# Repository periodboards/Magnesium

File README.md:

# Magnesium
My crappy 14-key macropad that contains many mistakes in the design

## Errors
### RGB backlighting doesn't work
Somehow in the many days that I had worked on routing the backlighting, I never noticed that I used the wrong LED footprint and so the leds are on the wrong side of the board

### The WS2812 was wired incorrectly
The power and ground were swapped on the WS2812, and therefore if you want to have underglow you need to use a bodge wire to connect data in to what was data out and rotate all of the LEDs accordingly

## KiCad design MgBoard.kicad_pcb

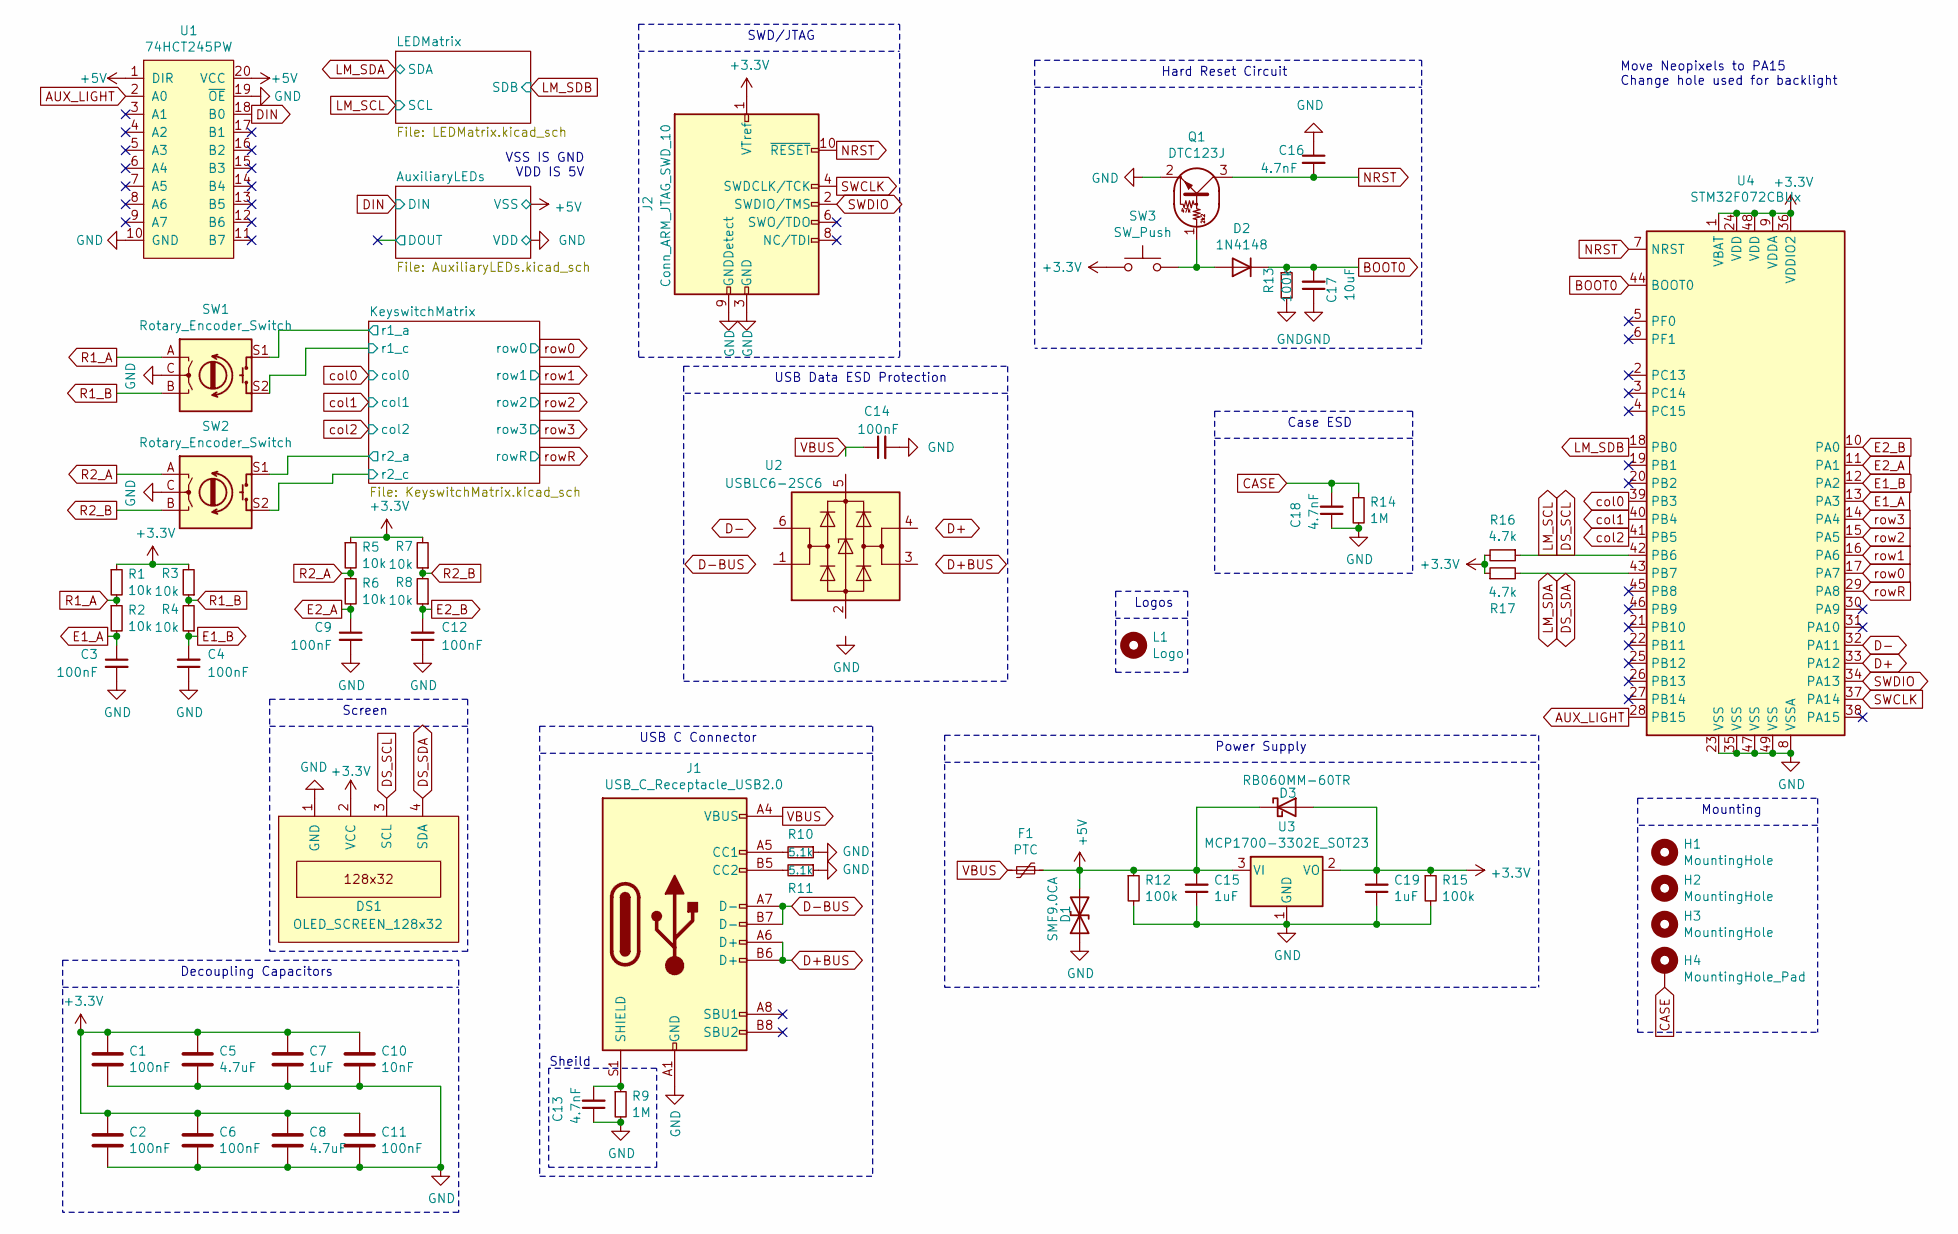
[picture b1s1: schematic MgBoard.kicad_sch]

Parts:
C1, C2, C3, C4, C6, C9, C11, C12, C14: 100nF; C_0603_1608Metric_Pad1.05x0.95mm_HandSolder
C5, C8: 4.7uF; C_0603_1608Metric_Pad1.05x0.95mm_HandSolder
C7, C15, C19: 1uF; C_0603_1608Metric_Pad1.05x0.95mm_HandSolder
C10: 10nF; C_0603_1608Metric_Pad1.05x0.95mm_HandSolder
C13, C16, C18: 4.7nF; C_0603_1608Metric_Pad1.05x0.95mm_HandSolder
C17: 10uF; C_0603_1608Metric_Pad1.05x0.95mm_HandSolder
D1: SMF9.0CA; D_SOD-123F
D2: 1N4148; D_SOD-123
D3: RB060MM-60TR; D_SOD-123F
DS1: OLED_SCREEN_128x32
F1: PTC; Fuse_1206_3216Metric_Pad1.42x1.75mm_HandSolder
H1, H2, H3: MountingHole; MountingHole_3.2mm_M3_ISO14580
H4: MountingHole_Pad; MountingHole_3.2mm_M3_ISO14580_Pad
J1: USB_C_Receptacle_USB2.0; USB_C_Receptacle_HRO_TYPE-C-31-M-12
J2: Conn_ARM_JTAG_SWD_10; PinHeader_2x05_P2.54mm_Vertical
L1: Logo; Mg
Q1: DTC123J; SOT-323_SC-70_Handsoldering
R1, R2, R3, R4, R5, R6, R7, R8: 10k; R_0603_1608Metric_Pad1.05x0.95mm_HandSolder
R9, R14: 1M; R_0603_1608Metric_Pad1.05x0.95mm_HandSolder
R10, R11: 5.1k; R_0603_1608Metric_Pad1.05x0.95mm_HandSolder
R12, R13, R15: 100k; R_0603_1608Metric_Pad1.05x0.95mm_HandSolder
R16, R17: 4.7k; R_0603_1608Metric_Pad1.05x0.95mm_HandSolder
SW1, SW2: Rotary_Encoder_Switch; RotaryEncoder_Alps_EC11E-Switch_Vertical_H20mm_1u
SW3: SW_Push; SW_SPST_SKQG_WithStem
U1: 74HCT245PW; TSSOP-20_4.4x6.5mm_P0.65mm
U2: USBLC6-2SC6; SOT-23-6_Handsoldering
U3: MCP1700-3302E_SOT23; SOT-23_Handsoldering
U4: STM32F072CBUx; QFN-48-1EP_7x7mm_P0.5mm_EP5.6x5.6mm

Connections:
+3V3: C1.1, C2.1, C5.1, C6.1, C7.1, C8.1, C10.1, C11.1, C19.2, D3.2 (A), DS1.2 (VCC), J2.1 (VTref), R1.1, R3.2, R5.1, R7.2, R15.1, R16.2, R17.1, SW3.1, U3.2 (VO), U4.1 (VBAT), U4.9 (VDDA), U4.24 (VDD), U4.36 (VDDIO2), U4.48 (VDD); also elsewhere on the board
+5V: C15.2, D1.2 (A2), D3.1 (K), F1.1, R12.1, U1.1 (DIR), U1.20 (VCC), U3.3 (VI); also elsewhere on the board
/KeyswitchMatrix/r1_c: SW1.S2; also elsewhere on the board
/KeyswitchMatrix/r2_c: SW2.S2; also elsewhere on the board
AUX_LIGHT: U1.2 (A0), U4.28 (PB15)
BOOT0: C17.2, D2.1 (K), R13.1, U4.44 (BOOT0)
CASE: C18.2, H4.1, R14.1
D+: U2.4 (I/O2), U4.33 (PA12)
D+BUS: J1.A6 (D+), J1.B6 (D+), U2.3 (I/O2)
D-: U2.6 (I/O1), U4.32 (PA11)
D-BUS: J1.A7 (D-), J1.B7 (D-), U2.1 (I/O1)
DIN: U1.18 (B0); also elsewhere on the board
DS_SCL: DS1.3 (SCL), R16.1, U4.42 (PB6); also elsewhere on the board
DS_SDA: DS1.4 (SDA), R17.2, U4.43 (PB7); also elsewhere on the board
E1_A: C3.1, R2.2, U4.13 (PA3)
E1_B: C4.2, R4.1, U4.12 (PA2)
E2_A: C9.1, R6.2, U4.11 (PA1)
E2_B: C12.2, R8.1, U4.10 (PA0)
GND: C1.2, C2.2, C3.2, C4.1, C5.2, C6.2, C7.2, C8.2, C9.2, C10.2, C11.2, C12.1, C13.1, C14.2, C15.1, C16.1, C17.1, C18.1, C19.1, D1.1 (A1), DS1.1 (GND), J1.A1 (GND), J1.A12 (GND), J1.B1 (GND), J1.B12 (GND), J2.3 (GND), J2.5 (GND), J2.9 (GNDDetect), Q1.2 (E), R9.2, R10.1, R11.1, R12.2, R13.2, R14.2, R15.2, SW1.C, SW2.C, U1.10 (GND), U1.19 (~OE), U2.2 (GND), U3.1 (GND), U4.8 (VSSA), U4.23 (VSS), U4.35 (VSS), U4.47 (VSS), U4.49 (VSS); also elsewhere on the board
LM_SDB: U4.18 (PB0); also elsewhere on the board
NRST: C16.2, J2.10 (~RESET~), Q1.3 (C), U4.7 (NRST)
unnamed: C13.2, J1.S1 (SHIELD), R9.1
unnamed: D2.2 (A), Q1.1 (B), SW3.2
unnamed: J1.A5 (CC1), R10.2
unnamed: J1.B5 (CC2), R11.2
R1_A: R1.2, R2.1, SW1.A
R1_B: R3.1, R4.2, SW1.B
R2_A: R5.2, R6.1, SW2.A
R2_B: R7.1, R8.2, SW2.B
SWCLK: J2.4 (SWDCLK/TCK), U4.37 (PA14)
SWDIO: J2.2 (SWDIO/TMS), U4.34 (PA13)
VBUS: C14.1, F1.2, J1.A4 (VBUS), J1.A9 (VBUS), J1.B4 (VBUS), J1.B9 (VBUS), U2.5 (VBUS)
col0: SW1.S1, U4.39 (PB3); also elsewhere on the board
col1: U4.40 (PB4); also elsewhere on the board
col2: SW2.S1, U4.41 (PB5); also elsewhere on the board
row0: U4.17 (PA7); also elsewhere on the board
row1: U4.16 (PA6); also elsewhere on the board
row2: U4.15 (PA5); also elsewhere on the board
row3: U4.14 (PA4); also elsewhere on the board
rowR: U4.29 (PA8); also elsewhere on the board

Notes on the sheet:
Decoupling Capacitors
Screen
Sheild
VSS IS GND VDD IS 5V
USB C Connector
SWD/JTAG
USB Data ESD Protection
Logos
Hard Reset Circuit
Power Supply
Case ESD
Move Neopixels to PA15 Change hole used for backlight
Mounting

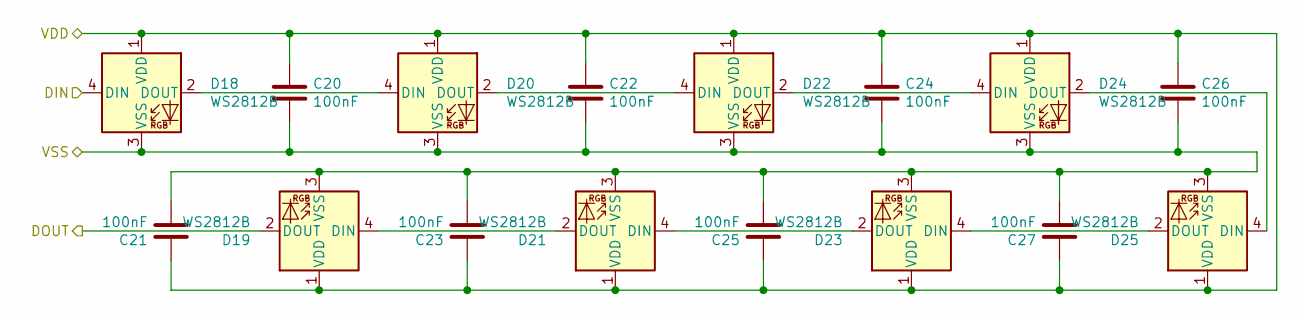
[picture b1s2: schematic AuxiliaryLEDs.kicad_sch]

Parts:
C20, C21, C22, C23, C24, C25, C26, C27: 100nF; C_0603_1608Metric_Pad1.05x0.95mm_HandSolder
D18, D19, D20, D21, D22, D23, D24, D25: WS2812B; LED_WS2812B_PLCC4_5.0x5.0mm_P3.2mm

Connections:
+5V: C20.1, C21.1, C22.1, C23.1, C24.1, C25.1, C26.1, C27.1, D18.3 (VSS), D19.3 (VSS), D20.3 (VSS), D21.3 (VSS), D22.3 (VSS), D23.3 (VSS), D24.3 (VSS), D25.3 (VSS); also elsewhere on the board
/AuxiliaryLEDs/DOUT: D19.2 (DOUT)
DIN: D18.4 (DIN); also elsewhere on the board
GND: C20.2, C21.2, C22.2, C23.2, C24.2, C25.2, C26.2, C27.2, D18.1 (VDD), D19.1 (VDD), D20.1 (VDD), D21.1 (VDD), D22.1 (VDD), D23.1 (VDD), D24.1 (VDD), D25.1 (VDD); also elsewhere on the board
unnamed: D18.2 (DOUT), D20.4 (DIN)
unnamed: D19.4 (DIN), D21.2 (DOUT)
unnamed: D20.2 (DOUT), D22.4 (DIN)
unnamed: D21.4 (DIN), D23.2 (DOUT)
unnamed: D22.2 (DOUT), D24.4 (DIN)
unnamed: D23.4 (DIN), D25.2 (DOUT)
unnamed: D24.2 (DOUT), D25.4 (DIN)

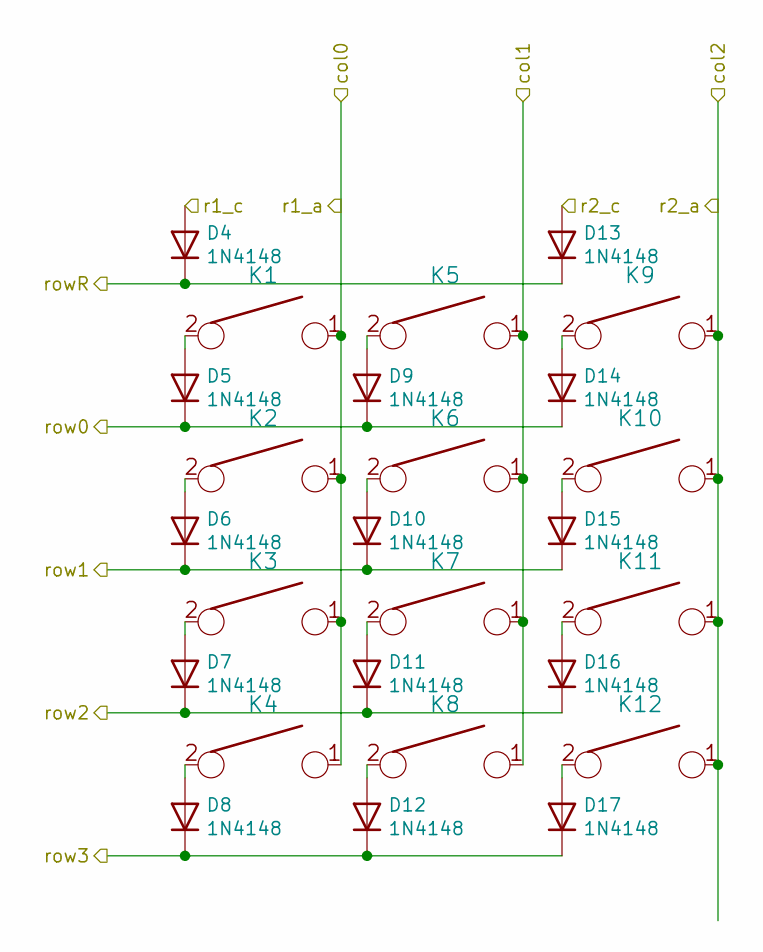
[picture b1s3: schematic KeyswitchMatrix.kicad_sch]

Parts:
D4, D5, D6, D7, D8, D9, D10, D11, D12, D13, D14, D15, D16, D17: 1N4148; D_SOD-123
K1, K2, K3, K4, K5, K6, K7, K8, K9, K10, K11, K12: KEYSW; Kailh_socket_MX_optional_1u

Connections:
/KeyswitchMatrix/r1_c: D4.2 (A); also elsewhere on the board
/KeyswitchMatrix/r2_c: D13.2 (A); also elsewhere on the board
unnamed: D5.2 (A), K1.2
unnamed: D6.2 (A), K2.2
unnamed: D7.2 (A), K3.2
unnamed: D8.2 (A), K4.2
unnamed: D9.2 (A), K5.2
unnamed: D10.2 (A), K6.2
unnamed: D11.2 (A), K7.2
unnamed: D12.2 (A), K8.2
unnamed: D14.2 (A), K9.2
unnamed: D15.2 (A), K10.2
unnamed: D16.2 (A), K11.2
unnamed: D17.2 (A), K12.2
col0: K1.1, K2.1, K3.1, K4.1; also elsewhere on the board
col1: K5.1, K6.1, K7.1, K8.1; also elsewhere on the board
col2: K9.1, K10.1, K11.1, K12.1; also elsewhere on the board
row0: D5.1 (K), D9.1 (K), D14.1 (K); also elsewhere on the board
row1: D6.1 (K), D10.1 (K), D15.1 (K); also elsewhere on the board
row2: D7.1 (K), D11.1 (K), D16.1 (K); also elsewhere on the board
row3: D8.1 (K), D12.1 (K), D17.1 (K); also elsewhere on the board
rowR: D4.1 (K), D13.1 (K); also elsewhere on the board

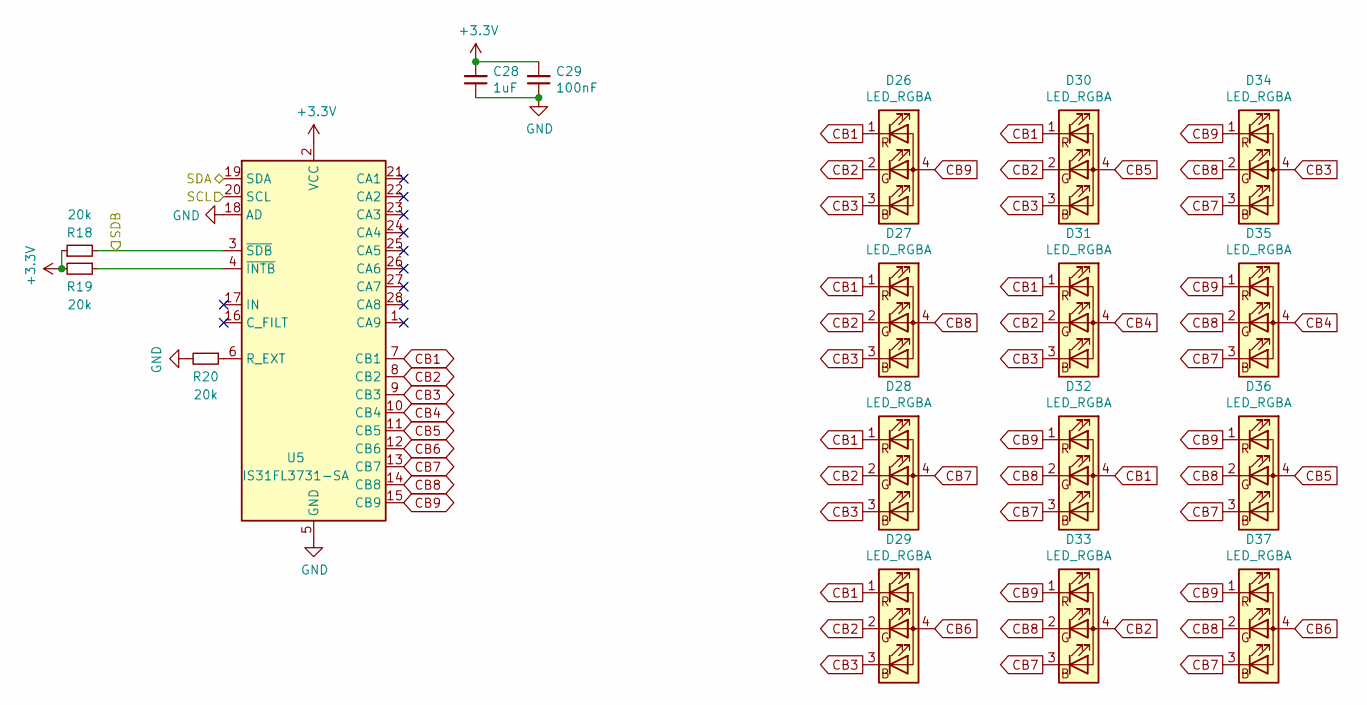
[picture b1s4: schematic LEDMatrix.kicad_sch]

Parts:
C28: 1uF; C_0603_1608Metric_Pad1.05x0.95mm_HandSolder
C29: 100nF; C_0603_1608Metric_Pad1.05x0.95mm_HandSolder
D26, D27, D28, D29, D30, D31, D32, D33, D34, D35, D36, D37: LED_RGBA; LED_RGBA_Reverse
R18, R19, R20: 20k; R_0603_1608Metric_Pad1.05x0.95mm_HandSolder
U5: IS31FL3731-SA; SSOP-28_5.3x10.2mm_P0.65mm

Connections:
+3V3: C28.2, C29.2, R18.1, R19.2, U5.2 (VCC); also elsewhere on the board
CB1: D26.1 (RK), D27.1 (RK), D28.1 (RK), D29.1 (RK), D30.1 (RK), D31.1 (RK), D32.4 (A), U5.7 (CB1)
CB2: D26.2 (GK), D27.2 (GK), D28.2 (GK), D29.2 (GK), D30.2 (GK), D31.2 (GK), D33.4 (A), U5.8 (CB2)
CB3: D26.3 (BK), D27.3 (BK), D28.3 (BK), D29.3 (BK), D30.3 (BK), D31.3 (BK), D34.4 (A), U5.9 (CB3)
CB4: D31.4 (A), D35.4 (A), U5.10 (CB4)
CB5: D30.4 (A), D36.4 (A), U5.11 (CB5)
CB6: D29.4 (A), D37.4 (A), U5.12 (CB6)
CB7: D28.4 (A), D32.3 (BK), D33.3 (BK), D34.3 (BK), D35.3 (BK), D36.3 (BK), D37.3 (BK), U5.13 (CB7)
CB8: D27.4 (A), D32.2 (GK), D33.2 (GK), D34.2 (GK), D35.2 (GK), D36.2 (GK), D37.2 (GK), U5.14 (CB8)
CB9: D26.4 (A), D32.1 (RK), D33.1 (RK), D34.1 (RK), D35.1 (RK), D36.1 (RK), D37.1 (RK), U5.15 (CB9)
DS_SCL: U5.20 (SCL); also elsewhere on the board
DS_SDA: U5.19 (SDA); also elsewhere on the board
GND: C28.1, C29.1, R20.2, U5.5 (GND), U5.18 (AD); also elsewhere on the board
LM_SDB: R18.2, U5.3 (~SDB); also elsewhere on the board
unnamed: R19.1, U5.4 (~INTB)
unnamed: R20.1, U5.6 (R_EXT)

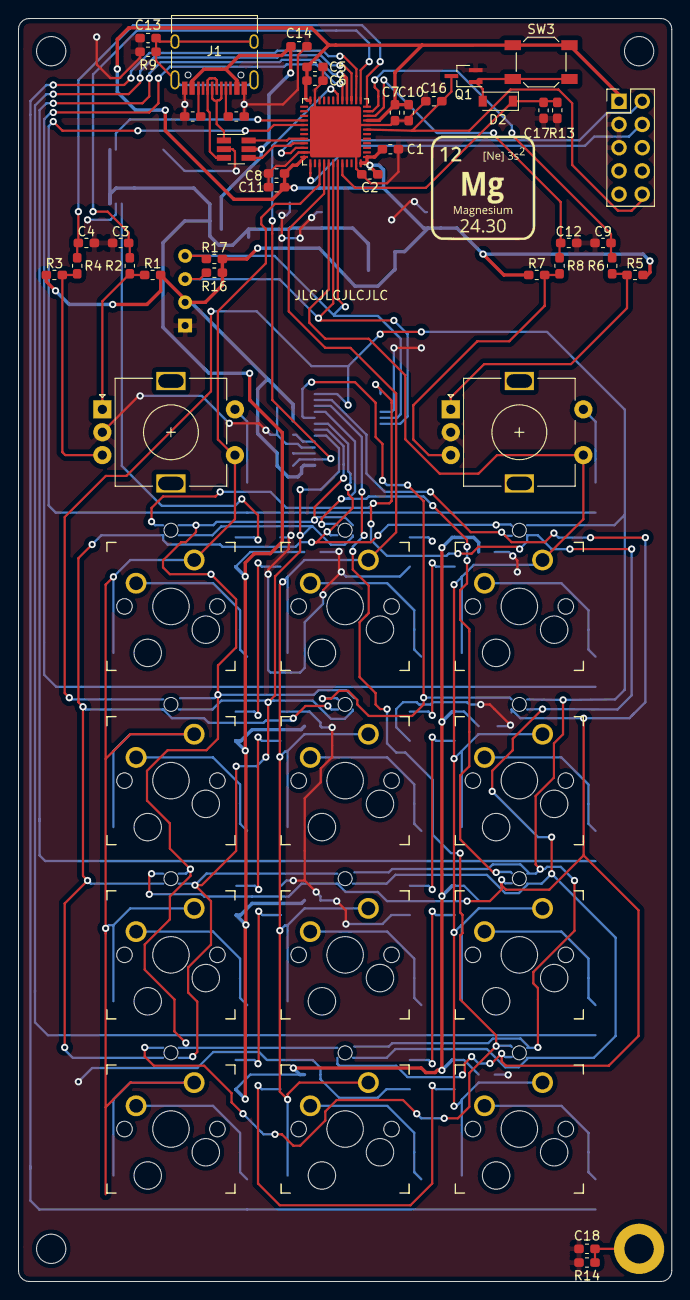
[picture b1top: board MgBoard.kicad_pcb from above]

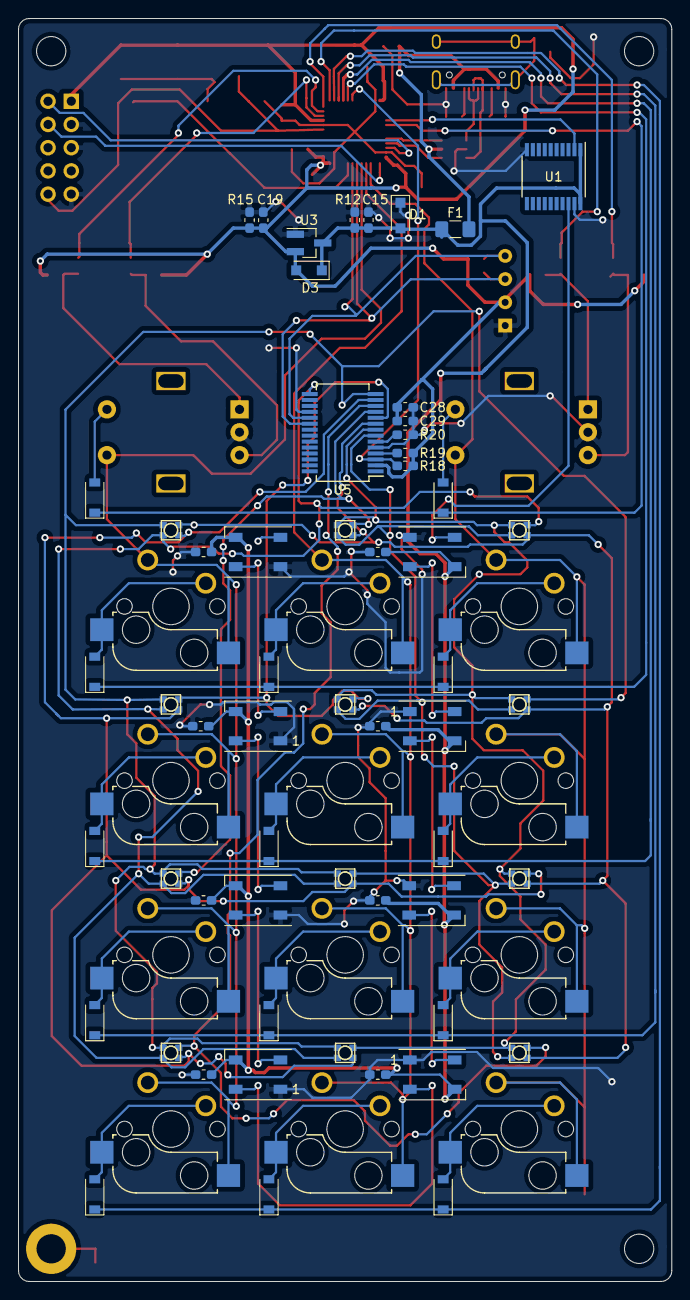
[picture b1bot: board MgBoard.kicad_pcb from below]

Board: 2 copper layers, 71.4 x 138.1 mm, 116 parts (45 on the bottom side), 70 nets.

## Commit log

2022-05-03 All of the crud
2022-05-03 Added 3d model of case and plate
2022-05-20 Start of kibot
2022-07-14 Latest
